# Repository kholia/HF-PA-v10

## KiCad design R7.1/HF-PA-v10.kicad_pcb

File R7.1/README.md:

Minor tweaks - previous versions are 100% fine ;)

List of changes:

- Various silkscreen improvements

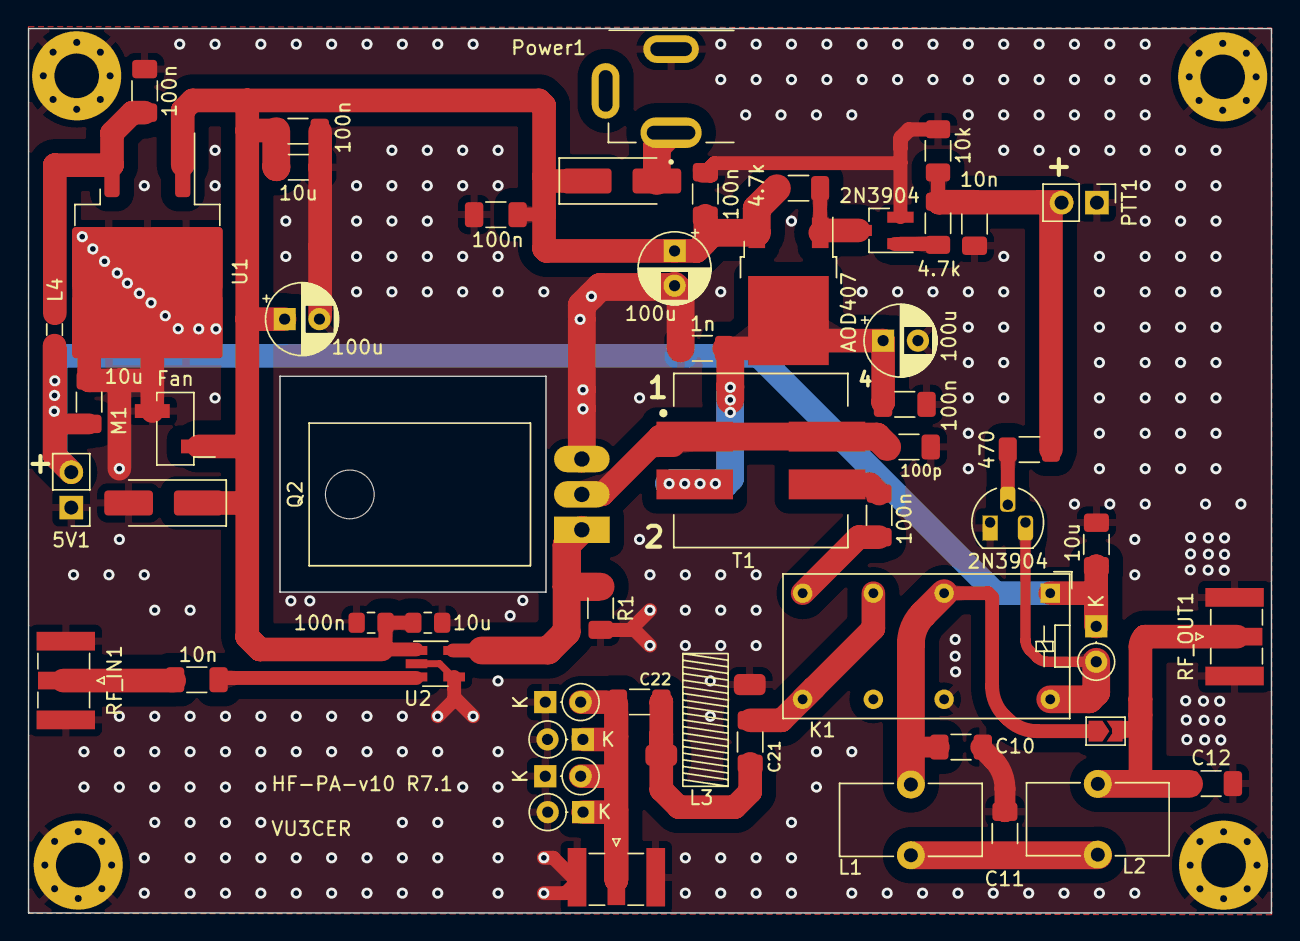
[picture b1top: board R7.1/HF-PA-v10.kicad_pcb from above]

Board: 2 copper layers, 89.2 x 63.5 mm, 59 parts (0 on the bottom side), 23 nets.

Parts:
5V1: 5V; PinHeader_1x02_P2.54mm_Vertical
C1, C6, C7, C9, C14, C18: 100n; C_1206_3216Metric_Pad1.33x1.80mm_HandSolder
C2, C8, C13: 10u; C_1206_3216Metric_Pad1.33x1.80mm_HandSolder
C3: 100p; C_1206_3216Metric_Pad1.33x1.80mm_HandSolder
C4, C19: 10n; C_1206_3216Metric_Pad1.33x1.80mm_HandSolder
C5, C15, C20: 100u; CP_Radial_D5.0mm_P2.50mm
C10, C12: 120p; C_1206_3216Metric_Pad1.33x1.80mm_HandSolder
C11: 200p; C_1206_3216Metric_Pad1.33x1.80mm_HandSolder
C16: 10u; C_0805_2012Metric_Pad1.18x1.45mm_HandSolder
C17: 1n; C_1206_3216Metric_Pad1.33x1.80mm_HandSolder
C21, C22: 470p; C_1206_3216Metric_Pad1.33x1.80mm_HandSolder
C23: 100n; C_0805_2012Metric_Pad1.18x1.45mm_HandSolder
D1: SS34; D_SMA_Handsoldering
D2: M7 (1N4007); D_SMA_Handsoldering
D3, D4, D5, D6, D7: 1N4148; D_DO-35_SOD27_P2.54mm_Vertical_KathodeUp
H1, H2, H3, H4: MountingHole_Pad; MountingHole_3.2mm_M3_Pad_Via
JP1: Jumper_2_Open; SolderJumper-2_P1.3mm_Open_TrianglePad1.0x1.5mm
K1: Omron G5V-2 / OEN 46-05-2C; Relay_DPDT_Omron_G5V-2
L1, L2: 360n; L_Toroid_Vertical_L10.0mm_W5.0mm_P5.08mm
L3: 1.02u; T37-2
L4: Ferrite Bead (2A); L_0805_2012Metric_Pad1.05x1.20mm_HandSolder
M1: Fan; PinHeader_1x02_P2.54mm_Vertical_SMD_Pin1Left
PTT1: PTT; PinHeader_1x02_P2.54mm_Vertical
Power1: DC-005 (Barrel Jack); XKB_DC-005-5A-2.0_Modded
Q1: 2N3904; TO-92_HandSolder
Q2: IRF510; TO-220-3_Horizontal_TabDown
Q3: AOD407; TO-252-2
Q4: 2N3904; SOT-23_Handsoldering
R1: 1M / 100K; R_1206_3216Metric_Pad1.30x1.75mm_HandSolder
R2: 10k; R_1206_3216Metric_Pad1.30x1.75mm_HandSolder
R4: 470; R_1206_3216Metric_Pad1.30x1.75mm_HandSolder
R8, R9: 4.7k; R_1206_3216Metric_Pad1.30x1.75mm_HandSolder
RF_IN1: SMA; SMA_Samtec_SMA-J-P-X-ST-EM1_EdgeMount
RF_OUT1: SMA; SMA_Samtec_SMA-J-P-X-ST-EM1_EdgeMount
RX1: SMA; SMA_Samtec_SMA-J-P-X-ST-EM1_EdgeMount
T1: Bifilar XFMR; IND_SRF1260A-4R7Y-Longer-Pads
U1: L7805 (D2PAK); TO-263-2
U2: UCC27517DBVR; SOT-23-5_HandSoldering

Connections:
12V: C1.1, C2.1, C14.1, C15.1, C16.1, C18.1, C20.1, C23.1, D1.1 (K), D2.1 (K), M1.1 (+), Q3.3 (S), R8.2, U1.1 (IN), U2.1 (VDD)
+5V: 5V1.2, C8.1, C13.1, D3.1 (K), K1.1, L4.1
+VDC: D1.2 (A), Power1.1
/DRAIN: C3.1, Q2.2 (D), T1.1, T1.4
GND: 5V1.1, C1.2, C2.2, C3.2, C4.2, C5.2, C6.2, C8.2, C9.2, C10.2, C11.2, C12.2, C13.2, C14.2, C15.2, C16.2, C17.2, C18.2, C20.2, C23.2, D2.2 (A), D4.1 (K), D5.2 (A), D6.1 (K), D7.2 (A), H1.1, H2.1, H3.1, H4.1, K1.13, L3.1, M1.2 (-), PTT1.1, Power1.2, Q1.1 (E), Q2.3 (S), Q4.2 (E), R1.2, R2.2, RF_IN1.2 (Ext), RF_OUT1.2 (Ext), RX1.2 (Ext), U1.2 (GND), U2.2 (GND), U2.4 (IN-)
LPF: C10.1, JP1.1 (A), K1.4, L1.1
unnamed: C7.2, T1.3
unnamed: C11.1, L1.2, L2.1
unnamed: C21.2, C22.1, L3.2
unnamed: D3.2 (A), K1.16, Q1.3 (C)
unnamed: C22.2, D4.2 (A), D5.1 (K), D6.2 (A), D7.1 (K), RX1.1 (In)
unnamed: C12.1, JP1.2 (B), L2.2, RF_OUT1.1 (In)
unnamed: Q1.2 (B), R4.2
unnamed: Q2.1 (G), R1.1, U2.5 (OUT)
unnamed: C5.1, C6.1, C17.1, Q3.2 (D), T1.2
unnamed: Q3.1 (G), Q4.3 (C), R8.1
unnamed: Q4.1 (B), R9.1
unnamed: C19.1, RF_IN1.1 (In)
unnamed: C9.1, L4.2, U1.3 (OUT)
unnamed: C19.2, U2.3 (IN+)
PTT: C4.1, PTT1.2, R2.1, R4.1, R9.2
RF_OUT: C7.1, K1.8
RX: C21.1, K1.6, K1.9

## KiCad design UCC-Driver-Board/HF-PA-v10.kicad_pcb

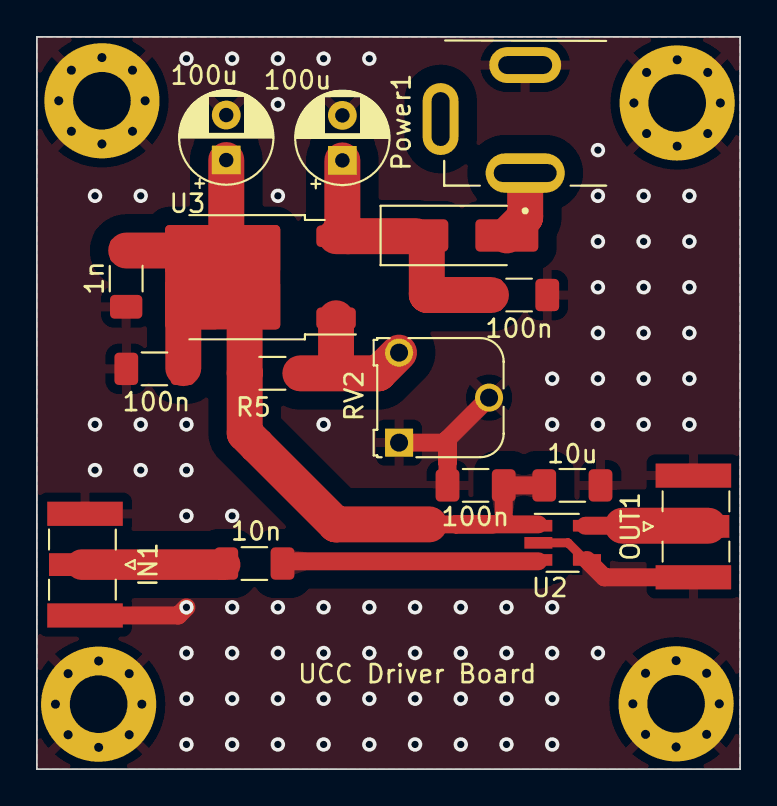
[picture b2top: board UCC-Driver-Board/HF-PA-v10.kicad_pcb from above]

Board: 2 copper layers, 39.1 x 40.7 mm, 20 parts (0 on the bottom side), 8 nets.

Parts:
C5, C15: 100u; CP_Radial_D5.0mm_P2.50mm
C6, C14, C23: 100n; C_1206_3216Metric_Pad1.33x1.80mm_HandSolder
C16: 10u; C_1206_3216Metric_Pad1.33x1.80mm_HandSolder
C17: 1n; C_1206_3216Metric_Pad1.33x1.80mm_HandSolder
C19: 10n; C_1206_3216Metric_Pad1.33x1.80mm_HandSolder
D1: SS34; D_SMA_Handsoldering
H1, H2, H3, H4: MountingHole_Pad; MountingHole_3.2mm_M3_Pad_Via
IN1: SMA; SMA_Samtec_SMA-J-P-X-ST-EM1_EdgeMount
OUT1: SMA; SMA_Samtec_SMA-J-P-X-ST-EM1_EdgeMount
Power1: DC-005 (Barrel Jack); XKB_DC-005-5A-2.0_Modded
R5: 220; R_1206_3216Metric_Pad1.30x1.75mm_HandSolder
RV2: 5k; Potentiometer_Runtron_RM-065_Vertical
U2: UCC27517DBVR; SOT-23-5_HandSoldering
U3: LM317_TO-252; TO-252-2

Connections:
12V: C5.1, C6.1, C16.1, C17.1, C23.1, R5.1, U2.1 (VDD), U3.2 (VO)
+VDC: D1.2 (A), Power1.1
GND: C5.2, C6.2, C14.2, C15.2, C16.2, C17.2, C23.2, H1.1, H2.1, H3.1, H4.1, IN1.2 (Ext), OUT1.2 (Ext), Power1.2, RV2.1, RV2.2, U2.2 (GND), U2.4 (IN-)
unnamed: C14.1, C15.1, D1.1 (K), U3.3 (VI)
unnamed: C19.1, IN1.1 (In)
unnamed: OUT1.1 (In), U2.5 (OUT)
unnamed: C19.2, U2.3 (IN+)
unnamed: R5.2, RV2.3, U3.1 (ADJ)
